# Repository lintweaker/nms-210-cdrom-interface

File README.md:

# nms-210-cdrom-interface
Recreation of the Philips NMS 210 CDROM interface for MSX

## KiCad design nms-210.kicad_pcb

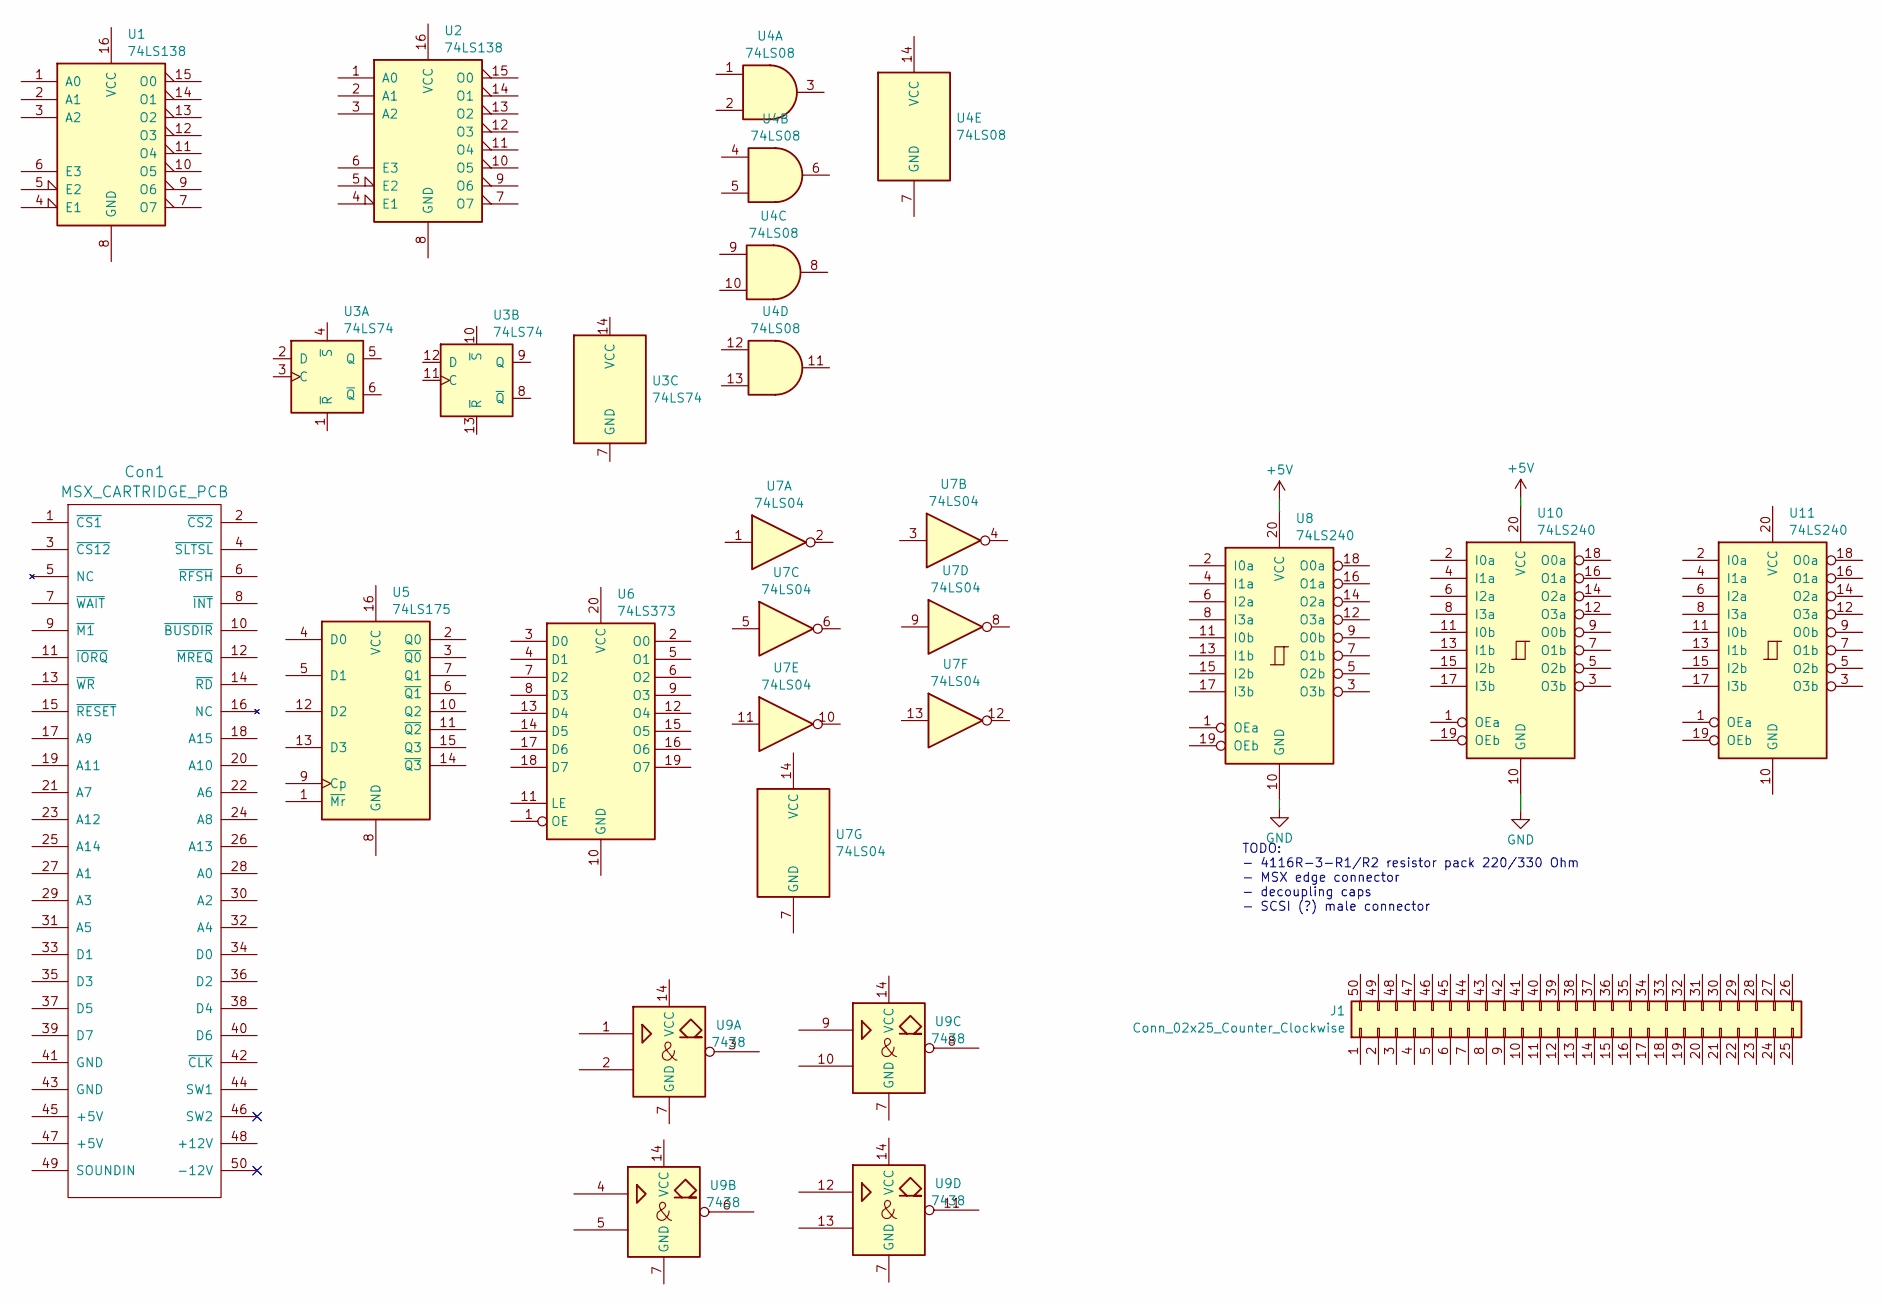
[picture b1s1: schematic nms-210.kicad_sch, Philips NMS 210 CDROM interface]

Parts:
Con1: MSX_CARTRIDGE_PCB; msx_cartridge
J1: Conn_02x25_Counter_Clockwise; PinHeader_2x25_P2.54mm_Horizontal
U1, U2: 74LS138; CERDIP-16_W7.62mm_SideBrazed
U3: 74LS74; CERDIP-14_W7.62mm_SideBrazed
U4: 74LS08; CERDIP-14_W7.62mm_SideBrazed
U5: 74LS175; CERDIP-16_W7.62mm_SideBrazed
U6: 74LS373; CERDIP-20_W7.62mm_SideBrazed
U7: 74LS04; CERDIP-14_W7.62mm_SideBrazed
U8, U10, U11: 74LS240; CERDIP-20_W7.62mm_SideBrazed
U9: 7438; CERDIP-14_W7.62mm_SideBrazed

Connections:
+5V: U8.20 (VCC), U10.20 (VCC)
GND: U8.10 (GND), U10.10 (GND)

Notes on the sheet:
TODO: - 4116R-3-R1/R2 resistor pack 220/330 Ohm - MSX edge connector - decoupling caps - SCSI (?) male connector

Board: 2 copper layers, 13 parts (0 on the bottom side), 2 nets, no tracks yet.

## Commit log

2024-06-16 Initial schematic and PCB setup
2024-10-29 Sync latest status
